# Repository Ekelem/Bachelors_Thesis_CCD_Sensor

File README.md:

# Bakalárska práca
Bakalárska práca VUT FIT, ROZŠIŘUJÍCÍ MODUL S CCD SENZOREM PRO VÝUKOVÝ KIT MINERVA

# Schémy

[Main](https://github.com/Ekelem/Bachelors_Thesis/blob/master/docs/ccdmodule.pdf)

[Image Sensor](https://github.com/Ekelem/Bachelors_Thesis/blob/master/docs/ImageSensor-Sheet5C7E7D75.pdf)

[Power Supply](https://github.com/Ekelem/Bachelors_Thesis/blob/master/docs/PowerSupply-Sheet5C7CB2BF.pdf)

# Preview

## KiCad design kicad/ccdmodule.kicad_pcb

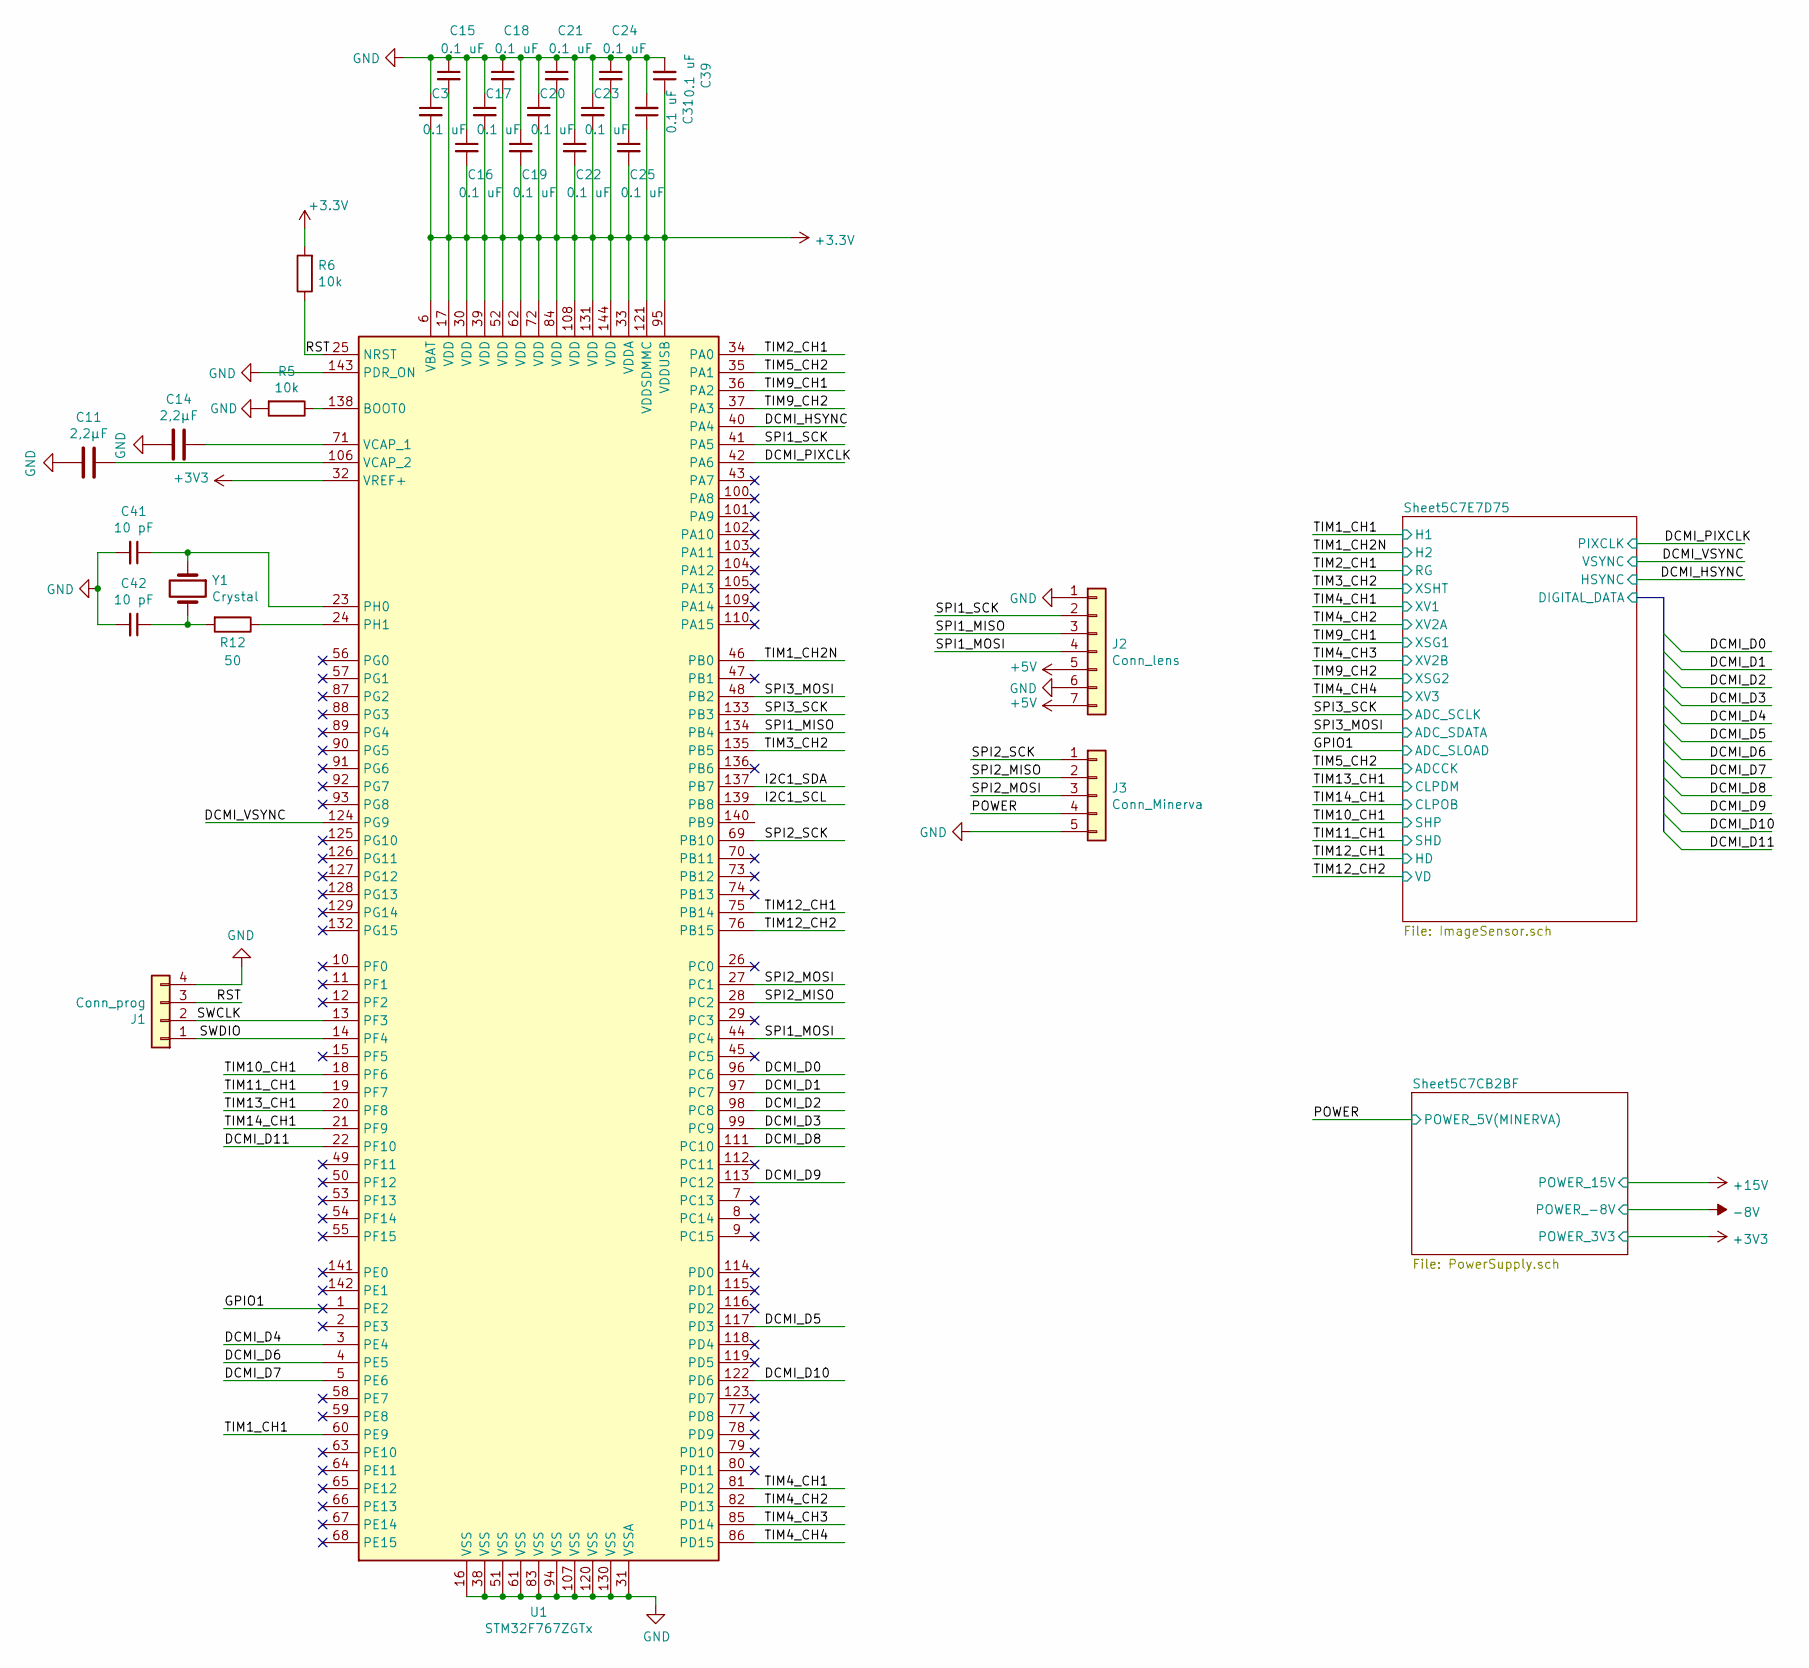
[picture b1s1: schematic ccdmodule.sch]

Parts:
C3, C15, C16, C17, C18, C19, C20, C21, C22, C23, C24, C25, C31, C39: 0.1 uF; C_0805_2012Metric
C11, C14: 2,2µF; C_1206_3216Metric
C41, C42: 10 pF; C_0201_0603Metric
J1: Conn_prog; PinHeader_1x04_P2.54mm_Vertical
J2: Conn_lens; PinHeader_1x07_P2.54mm_Vertical
J3: Conn_Minerva; PinHeader_1x05_P2.54mm_Vertical
R5, R6: 10k; R_0402_1005Metric
R12: 50; R_0402_1005Metric
U1: STM32F767ZGTx; LQFP-144_20x20mm_P0.5mm
Y1: Crystal; Crystal_SMD_5032-2Pin_5.0x3.2mm

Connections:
+3V3: C3.2, C15.2, C16.2, C17.2, C18.2, C19.2, C20.2, C21.2, C22.2, C23.2, C24.2, C25.2, C31.1, C39.1, R6.2, U1.6 (VBAT), U1.17 (VDD), U1.30 (VDD), U1.32 (VREF+), U1.33 (VDDA), U1.39 (VDD), U1.52 (VDD), U1.62 (VDD), U1.72 (VDD), U1.84 (VDD), U1.95 (VDDUSB), U1.108 (VDD), U1.121 (VDDSDMMC), U1.131 (VDD), U1.144 (VDD); also elsewhere on the board
+5V: J2.5, J2.7
/DCMI_D0: U1.96 (PC6)
/DCMI_D1: U1.97 (PC7)
/DCMI_D2: U1.98 (PC8)
/DCMI_D3: U1.99 (PC9)
/DCMI_D4: U1.3 (PE4)
/DCMI_D5: U1.117 (PD3)
/DCMI_D6: U1.4 (PE5)
/DCMI_D7: U1.5 (PE6)
/DCMI_D8: U1.111 (PC10)
/DCMI_D9: U1.113 (PC12)
/DCMI_D10: U1.122 (PD6)
/DCMI_D11: U1.22 (PF10)
/DCMI_HSYNC: U1.40 (PA4), U1.75 (PB14)
/DCMI_PIXCLK: U1.35 (PA1), U1.42 (PA6); also elsewhere on the board
/DCMI_VSYNC: U1.76 (PB15), U1.124 (PG9)
/GPIO1: U1.1 (PE2); also elsewhere on the board
/I2C1_SCL: U1.139 (PB8)
/I2C1_SDA: U1.137 (PB7)
/POWER: J3.4; also elsewhere on the board
/RST: J1.3, R6.1, U1.25 (NRST)
/SPI1_MISO: J2.3, U1.134 (PB4)
/SPI1_MOSI: J2.4, U1.44 (PC4)
/SPI1_SCK: J2.2, U1.41 (PA5)
/SPI2_MISO: J3.2, U1.28 (PC2)
/SPI2_MOSI: J3.3, U1.27 (PC1)
/SPI2_SCK: J3.1, U1.69 (PB10)
/SPI3_MOSI: U1.48 (PB2); also elsewhere on the board
/SPI3_SCK: U1.133 (PB3); also elsewhere on the board
/SWCLK: J1.2, U1.13 (PF3)
/SWDIO: J1.1, U1.14 (PF4)
/TIM1_CH1: U1.60 (PE9); also elsewhere on the board
/TIM1_CH2N: U1.46 (PB0); also elsewhere on the board
/TIM2_CH1: U1.34 (PA0); also elsewhere on the board
/TIM3_CH2: U1.135 (PB5); also elsewhere on the board
/TIM4_CH1: U1.81 (PD12); also elsewhere on the board
/TIM4_CH2: U1.82 (PD13); also elsewhere on the board
/TIM4_CH3: U1.85 (PD14); also elsewhere on the board
/TIM4_CH4: U1.86 (PD15); also elsewhere on the board
/TIM9_CH1: U1.36 (PA2); also elsewhere on the board
/TIM9_CH2: U1.37 (PA3); also elsewhere on the board
/TIM10_CH1: U1.18 (PF6); also elsewhere on the board
/TIM11_CH1: U1.19 (PF7); also elsewhere on the board
/TIM13_CH1: U1.20 (PF8); also elsewhere on the board
/TIM14_CH1: U1.21 (PF9); also elsewhere on the board
GND: C3.1, C11.1, C14.1, C15.1, C16.1, C17.1, C18.1, C19.1, C20.1, C21.1, C22.1, C23.1, C24.1, C25.1, C31.2, C39.2, C41.2, C42.2, J1.4, J2.1, J2.6, J3.5, R5.2, U1.16 (VSS), U1.31 (VSSA), U1.38 (VSS), U1.51 (VSS), U1.61 (VSS), U1.83 (VSS), U1.94 (VSS), U1.107 (VSS), U1.120 (VSS), U1.130 (VSS), U1.143 (PDR_ON); also elsewhere on the board
unnamed: C11.2, U1.106 (VCAP_2)
unnamed: C14.2, U1.71 (VCAP_1)
unnamed: C41.1, U1.23 (PH0), Y1.1
unnamed: C42.1, R12.2, Y1.2
unnamed: R5.1, U1.138 (BOOT0)
unnamed: R12.1, U1.24 (PH1)

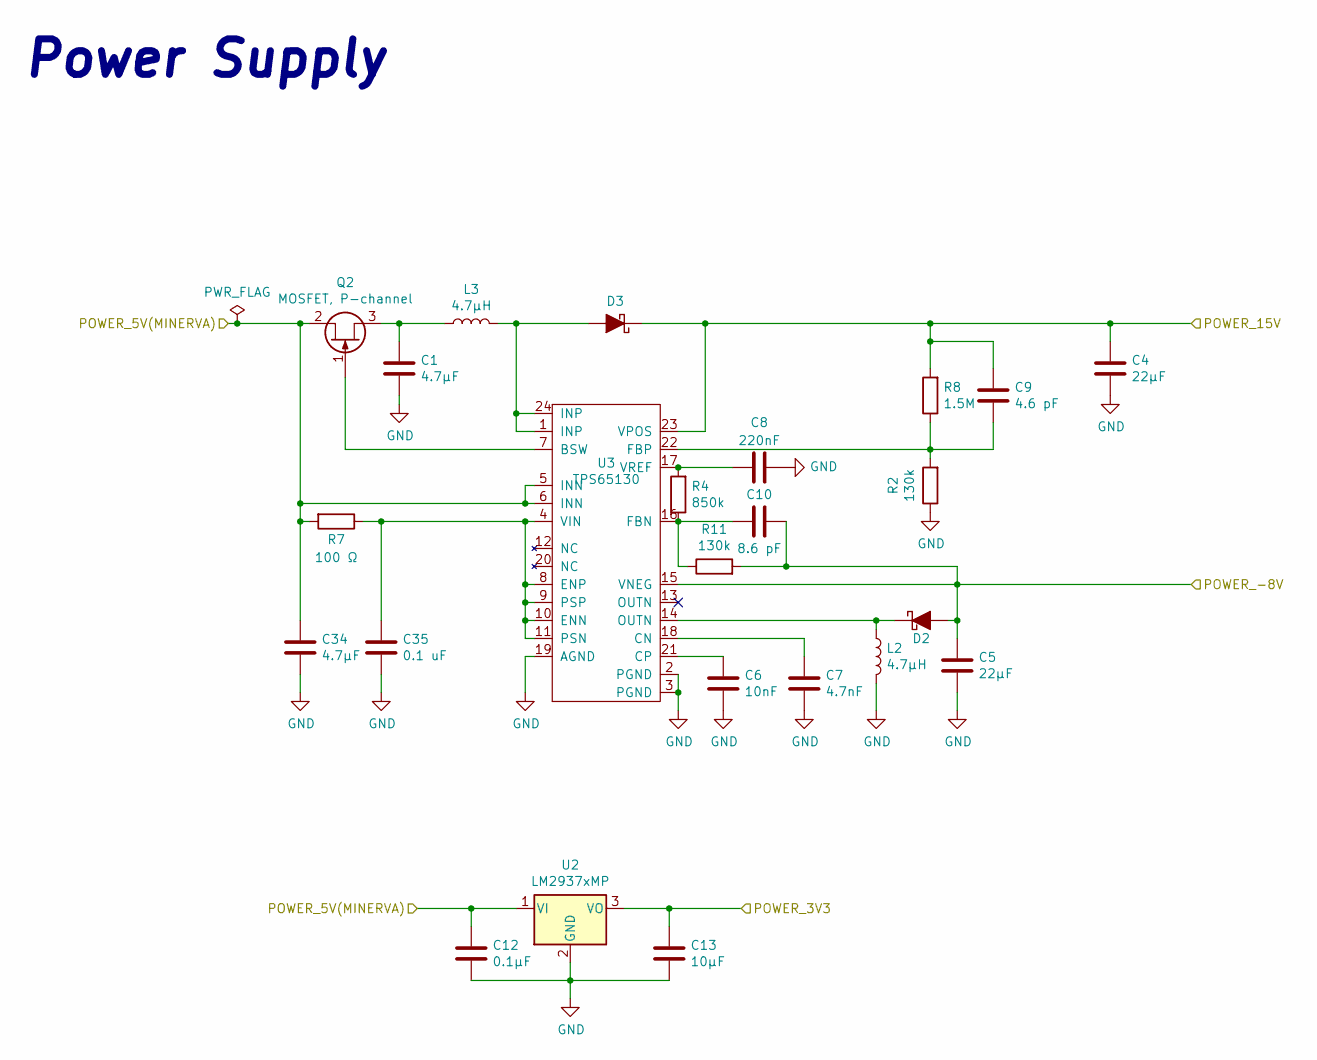
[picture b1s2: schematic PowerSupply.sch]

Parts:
C1: 4.7μF; C_1206_3216Metric
C4, C5: 22μF; C_0805_2012Metric
C6: 10nF; C_0805_2012Metric
C7: 4.7nF; C_0805_2012Metric
C8: 220nF; C_1206_3216Metric
C9: 4.6 pF; C_01005_0402Metric
C10: 8.6 pF; C_01005_0402Metric
C12: 0.1μF; C_1206_3216Metric
C13: 10μF; C_0805_2012Metric
C34: 4.7μF; C_0805_2012Metric
C35: 0.1 uF; C_0805_2012Metric
D2, D3: Schottky; D_SOD-123F
L2, L3: 4.7μH; L_Bourns-SRN4018
Q2: MOSFET, P-channel; SOT-23
R2, R11: 130k; R_0402_1005Metric
R4: 850k; R_0201_0603Metric
R7: 100 Ω; R_01005_0402Metric
R8: 1.5M; R_0201_0603Metric
U2: LM2937xMP; SOT-223-3_TabPin2
U3: TPS65130; QFN-24-1EP_4x4mm_P0.5mm_EP2.6x2.6mm

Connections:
+3V3: C13.1, U2.3 (VO); also elsewhere on the board
+15V: C4.1, C9.1, D3.1 (K), R8.2, U3.23 (VPOS); also elsewhere on the board
-8V: C5.1, C10.2, D2.2 (A), R11.2, U3.15 (VNEG); also elsewhere on the board
/POWER: C12.1, C34.1, Q2.2 (D), R7.2, U2.1 (VI), U3.5 (INN), U3.6 (INN); also elsewhere on the board
GND: C1.2, C4.2, C5.2, C6.2, C7.2, C8.1, C12.2, C13.2, C34.2, C35.2, L2.2, R2.1, U2.2 (GND), U3.2 (PGND), U3.3 (PGND), U3.19 (AGND); also elsewhere on the board
unnamed: C1.1, L3.1, Q2.3 (S)
unnamed: C6.1, U3.21 (CP)
unnamed: C7.1, U3.18 (CN)
unnamed: C8.2, R4.2, U3.17 (VREF)
unnamed: C9.2, R2.2, R8.1, U3.22 (FBP)
unnamed: C10.1, R4.1, R11.1, U3.16 (FBN)
unnamed: C35.1, R7.1, U3.4 (VIN), U3.8 (ENP), U3.9 (PSP), U3.10 (ENN), U3.11 (PSN)
unnamed: D2.1 (K), L2.1, U3.14 (OUTN)
unnamed: D3.2 (A), L3.2, U3.1 (INP), U3.24 (INP)
unnamed: Q2.1 (G), U3.7 (BSW)

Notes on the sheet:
Power Supply

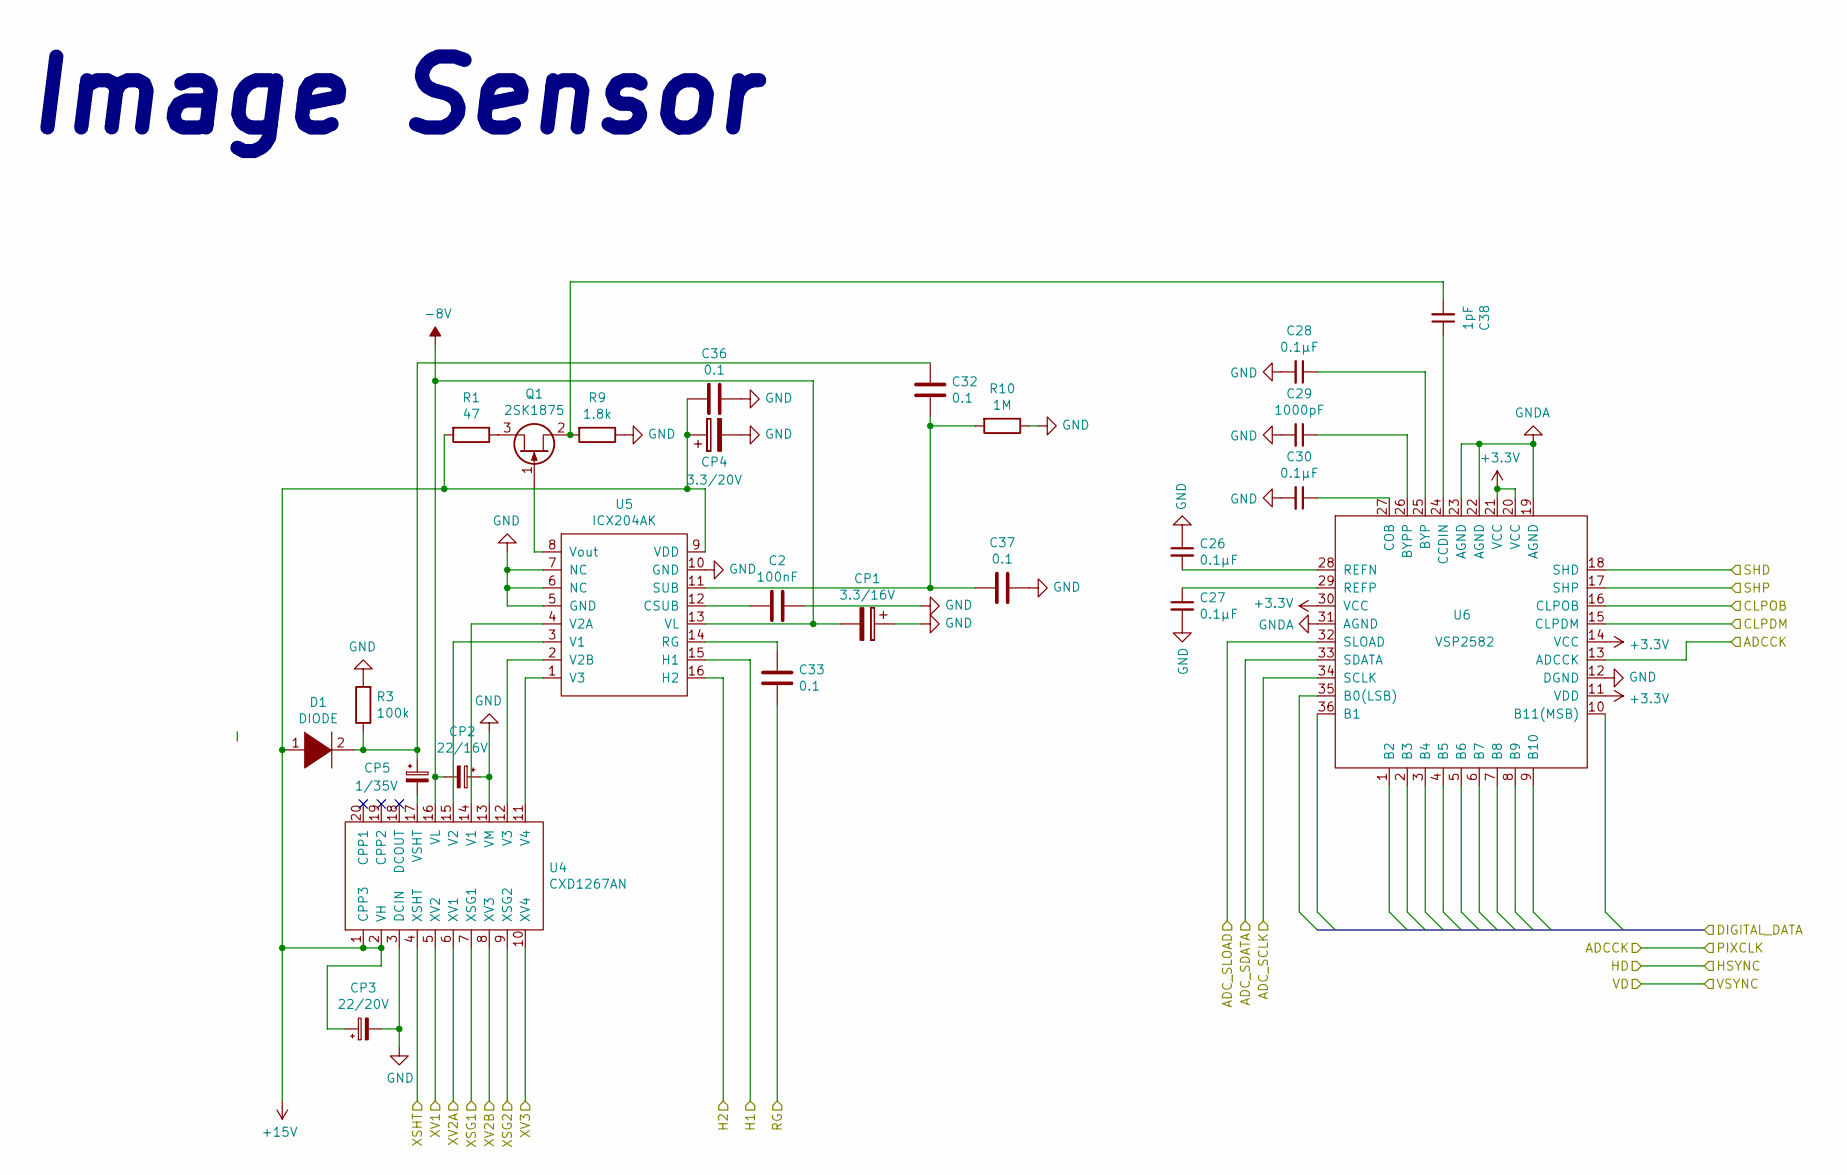
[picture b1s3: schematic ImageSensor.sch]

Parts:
C2: 100nF; C_1206_3216Metric
C26, C27, C28, C30: 0.1μF; C_0805_2012Metric
C29: 1000pF; C_0402_1005Metric
C32, C33, C36, C37: 0.1; C_0805_2012Metric
C38: 1pF; C_0603_1608Metric
CP1: 3.3/16V; CP_EIA-3528-12_Kemet-T
CP2: 22/16V; CP_EIA-7343-31_Kemet-D
CP3: 22/20V; CP_EIA-7343-31_Kemet-D
CP4: 3.3/20V; CP_EIA-3528-12_Kemet-T
CP5: 1/35V; CP_EIA-3528-21_Kemet-B
D1: DIODE; D_SOD-123
Q1: 2SK1875; SOT-323_SC-70
R1: 47; R_0201_0603Metric
R3: 100k; R_0805_2012Metric
R9: 1.8k; R_0201_0603Metric
R10: 1M; R_0402_1005Metric
U4: CXD1267AN; SSOP-20_4.4x6.5mm_P0.65mm
U5: ICX204AK; 16-DIP_sensor
U6: VSP2582; Texas_S-PVQFN-N36

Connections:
+3V3: U6.11 (VDD), U6.14 (VCC), U6.20 (VCC), U6.21 (VCC), U6.30 (VCC); also elsewhere on the board
+15V: C36.1, CP3.1, CP4.1, D1.1 (K), R1.2, U4.1 (CPP3), U4.2 (VH), U5.9 (VDD); also elsewhere on the board
-8V: CP1.2, CP2.2, U4.16 (VL), U5.13 (VL); also elsewhere on the board
/DCMI_PIXCLK: U6.13 (ADCCK); also elsewhere on the board
/GPIO1: U6.32 (SLOAD); also elsewhere on the board
/SPI3_MOSI: U6.33 (SDATA); also elsewhere on the board
/SPI3_SCK: U6.34 (SCLK); also elsewhere on the board
/TIM1_CH1: U5.15 (H1); also elsewhere on the board
/TIM1_CH2N: U5.16 (H2); also elsewhere on the board
/TIM2_CH1: C33.2; also elsewhere on the board
/TIM3_CH2: U4.4 (XSHT); also elsewhere on the board
/TIM4_CH1: U4.5 (XV2); also elsewhere on the board
/TIM4_CH2: U4.6 (XV1); also elsewhere on the board
/TIM4_CH3: U4.8 (XV3); also elsewhere on the board
/TIM4_CH4: U4.10 (XV4); also elsewhere on the board
/TIM9_CH1: U4.7 (XSG1); also elsewhere on the board
/TIM9_CH2: U4.9 (XSG2); also elsewhere on the board
/TIM10_CH1: U6.17 (SHP); also elsewhere on the board
/TIM11_CH1: U6.18 (SHD); also elsewhere on the board
/TIM13_CH1: U6.15 (CLPDM); also elsewhere on the board
/TIM14_CH1: U6.16 (CLPOB); also elsewhere on the board
GND: C2.1, C26.1, C27.2, C28.2, C29.2, C30.2, C36.2, C37.1, CP1.1, CP2.1, CP3.2, CP4.2, R3.2, R9.1, R10.1, U4.3 (DCIN), U4.13 (VM), U5.5 (GND), U5.6 (NC), U5.7 (NC), U5.10 (GND), U6.12 (DGND); also elsewhere on the board
GNDA: U6.19 (AGND), U6.22 (AGND), U6.23 (AGND), U6.31 (AGND)
unnamed: C2.2, U5.12 (CSUB)
unnamed: C26.2, U6.28 (REFN)
unnamed: C27.1, U6.29 (REFP)
unnamed: C28.1, U6.25 (BYP)
unnamed: C29.1, U6.26 (BYPP)
unnamed: C30.1, U6.27 (COB)
unnamed: C32.1, C37.2, R10.2, U5.11 (SUB)
unnamed: C32.2, CP5.1, D1.2 (A), R3.1
unnamed: C33.1, U5.14 (RG)
unnamed: C38.1, U6.24 (CCDIN)
unnamed: C38.2, Q1.2 (S), R9.2
unnamed: CP5.2, U4.17 (VSHT)
unnamed: Q1.1 (G), U5.8 (Vout)
unnamed: Q1.3 (D), R1.1
unnamed: U4.11 (V4), U5.1 (V3)
unnamed: U4.12 (V3), U5.2 (V2B)
unnamed: U4.14 (V1), U5.4 (V2A)
unnamed: U4.15 (V2), U5.3 (V1)

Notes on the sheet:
Image Sensor

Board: 2 copper layers, 76 parts (0 on the bottom side), 70 nets, no tracks yet.

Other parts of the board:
C40: 4.7 uF; C_1206_3216Metric

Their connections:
+3V3: C40.1; also elsewhere on the board
GND: C40.2; also elsewhere on the board

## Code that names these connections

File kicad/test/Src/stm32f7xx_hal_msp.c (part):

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    PE5     ------> DCMI_D6
    PE6     ------> DCMI_D7
    PF10     ------> DCMI_D11
    PA4     ------> DCMI_HSYNC
    PA6     ------> DCMI_PIXCLK
    PC6     ------> DCMI_D0
    PC7     ------> DCMI_D1
    PC8     ------> DCMI_D2
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    PC12     ------> DCMI_D9
    PD3     ------> DCMI_D5
    PD6     ------> DCMI_D10
    PG9     ------> DCMI_VSYNC 
    */
    GPIO_InitStruct.Pin = GPIO_PIN_4|GPIO_PIN_5|GPIO_PIN_6;
    GPIO_InitStruct.Mode = GPIO_MODE_AF_PP;
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    PE5     ------> DCMI_D6
    PE6     ------> DCMI_D7
    PF10     ------> DCMI_D11
    PA4     ------> DCMI_HSYNC
    PA6     ------> DCMI_PIXCLK
    PC6     ------> DCMI_D0
    PC7     ------> DCMI_D1
    PC8     ------> DCMI_D2
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    PC12     ------> DCMI_D9
    PD3     ------> DCMI_D5
    PD6     ------> DCMI_D10
    PG9     ------> DCMI_VSYNC 
    */
    HAL_GPIO_DeInit(GPIOE, GPIO_PIN_4|GPIO_PIN_5|GPIO_PIN_6);

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    __HAL_RCC_GPIOG_CLK_ENABLE();
    __HAL_RCC_GPIOB_CLK_ENABLE();
    /**SPI1 GPIO Configuration    
    PD7     ------> SPI1_MOSI
    PG11     ------> SPI1_SCK
    PB4     ------> SPI1_MISO 
    */
    GPIO_InitStruct.Pin = GPIO_PIN_7;
    GPIO_InitStruct.Mode = GPIO_MODE_AF_PP;
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    __HAL_RCC_GPIOC_CLK_ENABLE();
    __HAL_RCC_GPIOB_CLK_ENABLE();
    /**SPI2 GPIO Configuration    
    PC1     ------> SPI2_MOSI
    PC2     ------> SPI2_MISO
    PB10     ------> SPI2_SCK 
    */
    GPIO_InitStruct.Pin = GPIO_PIN_1|GPIO_PIN_2;
    GPIO_InitStruct.Mode = GPIO_MODE_AF_PP;
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    __HAL_RCC_SPI1_CLK_DISABLE();
  
    /**SPI1 GPIO Configuration    
    PD7     ------> SPI1_MOSI
    PG11     ------> SPI1_SCK
    PB4     ------> SPI1_MISO 
    */
    HAL_GPIO_DeInit(GPIOD, GPIO_PIN_7);

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    __HAL_RCC_SPI2_CLK_DISABLE();
  
    /**SPI2 GPIO Configuration    
    PC1     ------> SPI2_MOSI
    PC2     ------> SPI2_MISO
    PB10     ------> SPI2_SCK 
    */
    HAL_GPIO_DeInit(GPIOC, GPIO_PIN_1|GPIO_PIN_2);

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  
    __HAL_RCC_GPIOA_CLK_ENABLE();
    /**TIM2 GPIO Configuration    
    PA5     ------> TIM2_CH1 
    */
    GPIO_InitStruct.Pin = GPIO_PIN_5;
    GPIO_InitStruct.Mode = GPIO_MODE_AF_PP;
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  
    __HAL_RCC_GPIOA_CLK_ENABLE();
    /**TIM3 GPIO Configuration    
    PA7     ------> TIM3_CH2 
    */
    GPIO_InitStruct.Pin = GPIO_PIN_7;
    GPIO_InitStruct.Mode = GPIO_MODE_AF_PP;
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    __HAL_RCC_GPIOB_CLK_ENABLE();
    __HAL_RCC_GPIOE_CLK_ENABLE();
    /**TIM1 GPIO Configuration    
    PB0     ------> TIM1_CH2N
    PE9     ------> TIM1_CH1 
    */
    GPIO_InitStruct.Pin = GPIO_PIN_0;
    GPIO_InitStruct.Mode = GPIO_MODE_AF_PP;
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  
    __HAL_RCC_GPIOD_CLK_ENABLE();
    /**TIM4 GPIO Configuration    
    PD12     ------> TIM4_CH1
    PD13     ------> TIM4_CH2
    PD14     ------> TIM4_CH3
    PD15     ------> TIM4_CH4 
    */
    GPIO_InitStruct.Pin = GPIO_PIN_12|GPIO_PIN_13|GPIO_PIN_14|GPIO_PIN_15;
    GPIO_InitStruct.Mode = GPIO_MODE_AF_PP;
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  
    __HAL_RCC_GPIOA_CLK_ENABLE();
    /**TIM5 GPIO Configuration    
    PA0/WKUP     ------> TIM5_CH1
    PA1     ------> TIM5_CH2 
    */
    GPIO_InitStruct.Pin = GPIO_PIN_0|GPIO_PIN_1;
    GPIO_InitStruct.Mode = GPIO_MODE_AF_PP;
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  
    __HAL_RCC_GPIOA_CLK_ENABLE();
    /**TIM9 GPIO Configuration    
    PA2     ------> TIM9_CH1
    PA3     ------> TIM9_CH2 
    */
    GPIO_InitStruct.Pin = GPIO_PIN_2|GPIO_PIN_3;
    GPIO_InitStruct.Mode = GPIO_MODE_AF_PP;
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  
    __HAL_RCC_GPIOF_CLK_ENABLE();
    /**TIM10 GPIO Configuration    
    PF6     ------> TIM10_CH1 
    */
    GPIO_InitStruct.Pin = GPIO_PIN_6;
    GPIO_InitStruct.Mode = GPIO_MODE_AF_PP;
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  
    __HAL_RCC_GPIOF_CLK_ENABLE();
    /**TIM11 GPIO Configuration    
    PF7     ------> TIM11_CH1 
    */
    GPIO_InitStruct.Pin = GPIO_PIN_7;
    GPIO_InitStruct.Mode = GPIO_MODE_AF_PP;
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  
    __HAL_RCC_GPIOB_CLK_ENABLE();
    /**TIM12 GPIO Configuration    
    PB14     ------> TIM12_CH1
    PB15     ------> TIM12_CH2 
    */
    GPIO_InitStruct.Pin = GPIO_PIN_14|GPIO_PIN_15;
    GPIO_InitStruct.Mode = GPIO_MODE_AF_PP;
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  
    __HAL_RCC_GPIOF_CLK_ENABLE();
    /**TIM13 GPIO Configuration    
    PF8     ------> TIM13_CH1 
    */
    GPIO_InitStruct.Pin = GPIO_PIN_8;
    GPIO_InitStruct.Mode = GPIO_MODE_AF_PP;
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  
    __HAL_RCC_GPIOF_CLK_ENABLE();
    /**TIM14 GPIO Configuration    
    PF9     ------> TIM14_CH1 
    */
    GPIO_InitStruct.Pin = GPIO_PIN_9;
    GPIO_InitStruct.Mode = GPIO_MODE_AF_PP;
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    __HAL_RCC_TIM2_CLK_DISABLE();
  
    /**TIM2 GPIO Configuration    
    PA5     ------> TIM2_CH1 
    */
    HAL_GPIO_DeInit(GPIOA, GPIO_PIN_5);

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    __HAL_RCC_TIM3_CLK_DISABLE();
  
    /**TIM3 GPIO Configuration    
    PA7     ------> TIM3_CH2 
    */
    HAL_GPIO_DeInit(GPIOA, GPIO_PIN_7);

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
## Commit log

2019-02-28 Notes added
2019-03-03 image sensor datasheets
2019-09-04 3d preview image
2019-09-04 schemes
2019-09-04 kicad project files
2019-09-04 Readme.md added links
2019-09-04 readme.md path fix

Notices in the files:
kicad/test/Src/stm32f7xx_hal_msp.c:
© Copyright (c) 2019 STMicroelectronics.
All rights reserved.
This software component is licensed by ST under BSD 3-Clause license,
the "License"; You may not use this file except in compliance with the
License. You may obtain a copy of the License at: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
(C) COPYRIGHT STMicroelectronics *****END OF FILE
